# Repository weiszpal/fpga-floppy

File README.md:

# fpga-floppy
FPGA interface board to use an IBM PC floppy disk drive as any C64 comatible FDD

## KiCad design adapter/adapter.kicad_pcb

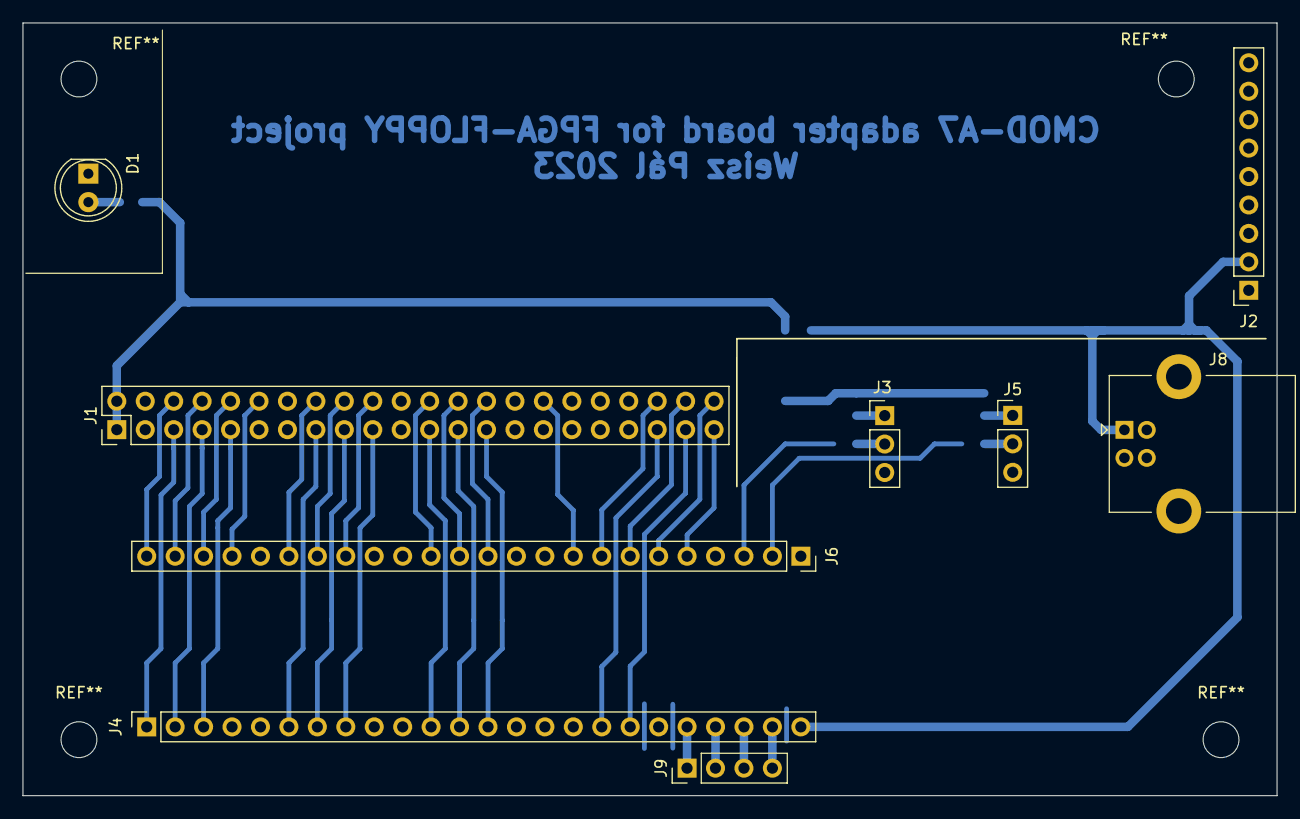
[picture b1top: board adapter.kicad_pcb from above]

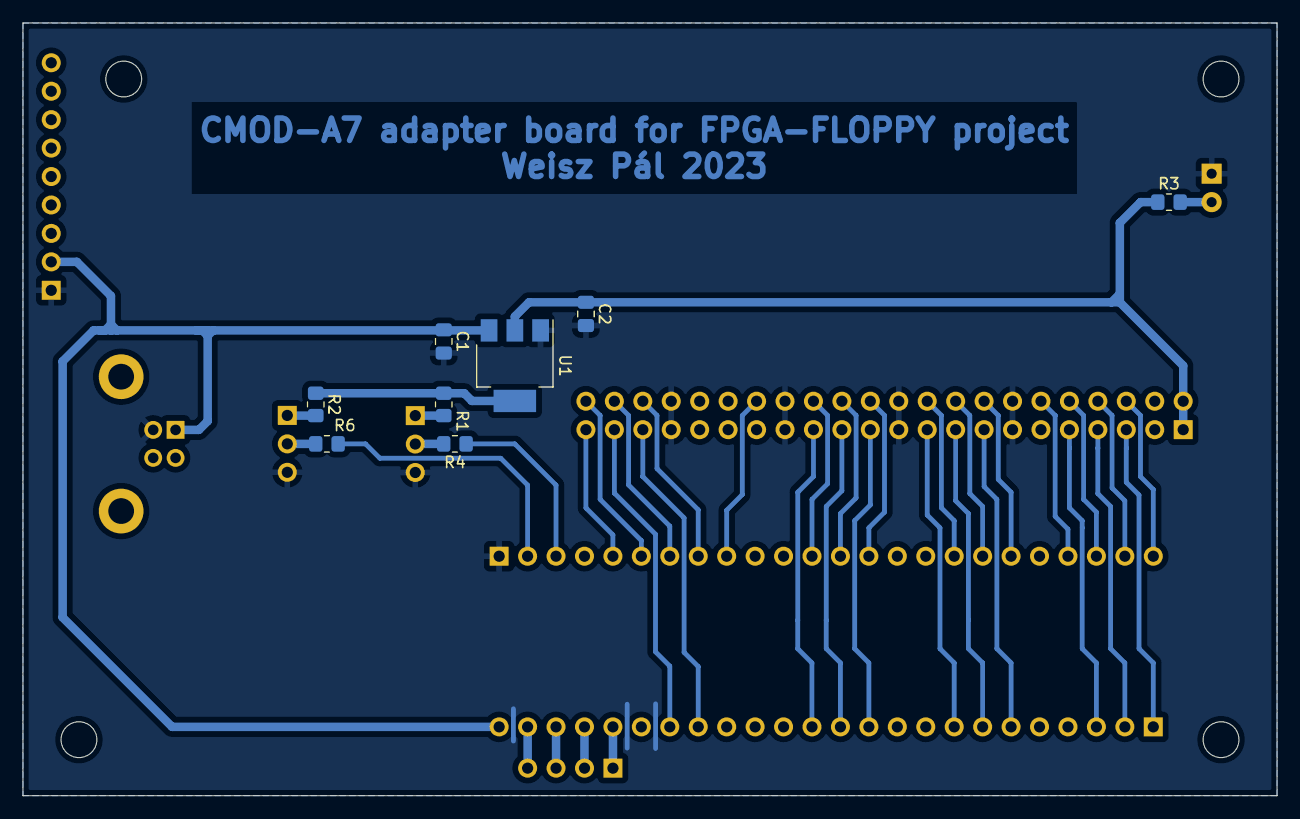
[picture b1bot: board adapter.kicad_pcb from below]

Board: 2 copper layers, 112.0 x 69.0 mm, 17 parts (8 on the bottom side), 40 nets.

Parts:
C1: 100n; C_0805_2012Metric_Pad1.18x1.45mm_HandSolder
C2: 10u; C_0805_2012Metric_Pad1.18x1.45mm_HandSolder
D1: LED_Filled; LED_D5.0mm
J1: FPGA_devboard; PinHeader_2x22_P2.54mm_Vertical
J2: 5V_PWR; PinSocket_1x09_P2.54mm_Vertical
J3: JP1; PinHeader_1x03_P2.54mm_Vertical
J4: CMOD-A7 1; PinSocket_1x24_P2.54mm_Vertical
J5: JP2; PinHeader_1x03_P2.54mm_Vertical
J6: CMOD-A7 2; PinSocket_1x24_P2.54mm_Vertical
J8: USB_B; USB_B_Lumberg_2411_02_Horizontal
J9: DEBUG; PinHeader_1x04_P2.54mm_Vertical
R1, R2, R4, R6: 10k; R_0805_2012Metric_Pad1.20x1.40mm_HandSolder
R3: 1k; R_0805_2012Metric_Pad1.20x1.40mm_HandSolder
U1: AP1117-33; SOT-223-3_TabPin2

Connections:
+3V3: C2.1, J1.1, J1.2, R1.1, R2.1, R3.1, U1.2 (VO)
+5V: C1.1, J2.2, J4.24, J8.1 (VBUS), U1.3 (VI)
/ACTION: J1.5, J4.1
/ATN_IN: J1.7, J4.2
/CLK_IN: J1.9, J4.3
/CLK_OUT: J1.15, J4.6
/DATA_IN: J1.12, J6.21
/DATA_OUT: J1.16, J6.19
/DIR: J1.39, J4.17
/DRVSA: J1.41, J4.18
/DRVSB: J1.42, J6.7
/DSKCHG: J1.24, J6.14
/INDEX: J1.27, J4.13
/MOTEA: J1.43, J6.5
/MOTEB: J1.40, J6.8
/PIO07: J1.17, J4.7
/PIO08: J1.19, J4.8
/PIO11: J1.23, J4.11
/PIO12: J1.25, J4.12
/PIO20: J4.20, J9.1
/PIO21: J4.21, J9.2
/PIO22: J4.22, J9.3
/PIO23: J4.23, J9.4
/PIO26: J6.2, R6.2
/PIO27: J6.3, R4.1
/PIO30: J1.44, J6.6
/PIO33: J1.32, J6.9
/PIO36: J1.28, J6.12
/PIO37: J1.26, J6.13
/PIO41: J1.20, J6.17
/PIO42: J1.18, J6.18
/PIO46: J1.10, J6.22
/PIO47: J1.8, J6.23
/PIO48: J1.6, J6.24
GND: C1.2, C2.2, D1.1 (K), J1.13, J1.14, J1.21, J1.22, J1.29, J1.30, J1.37, J1.38, J2.1, J3.3, J5.3, J6.1, J8.4 (GND), U1.1 (GND)
unnamed: D1.2 (A), R3.2
unnamed: J3.1, R1.2
unnamed: J3.2, R4.2
unnamed: J5.1, R2.2
unnamed: J5.2, R6.1

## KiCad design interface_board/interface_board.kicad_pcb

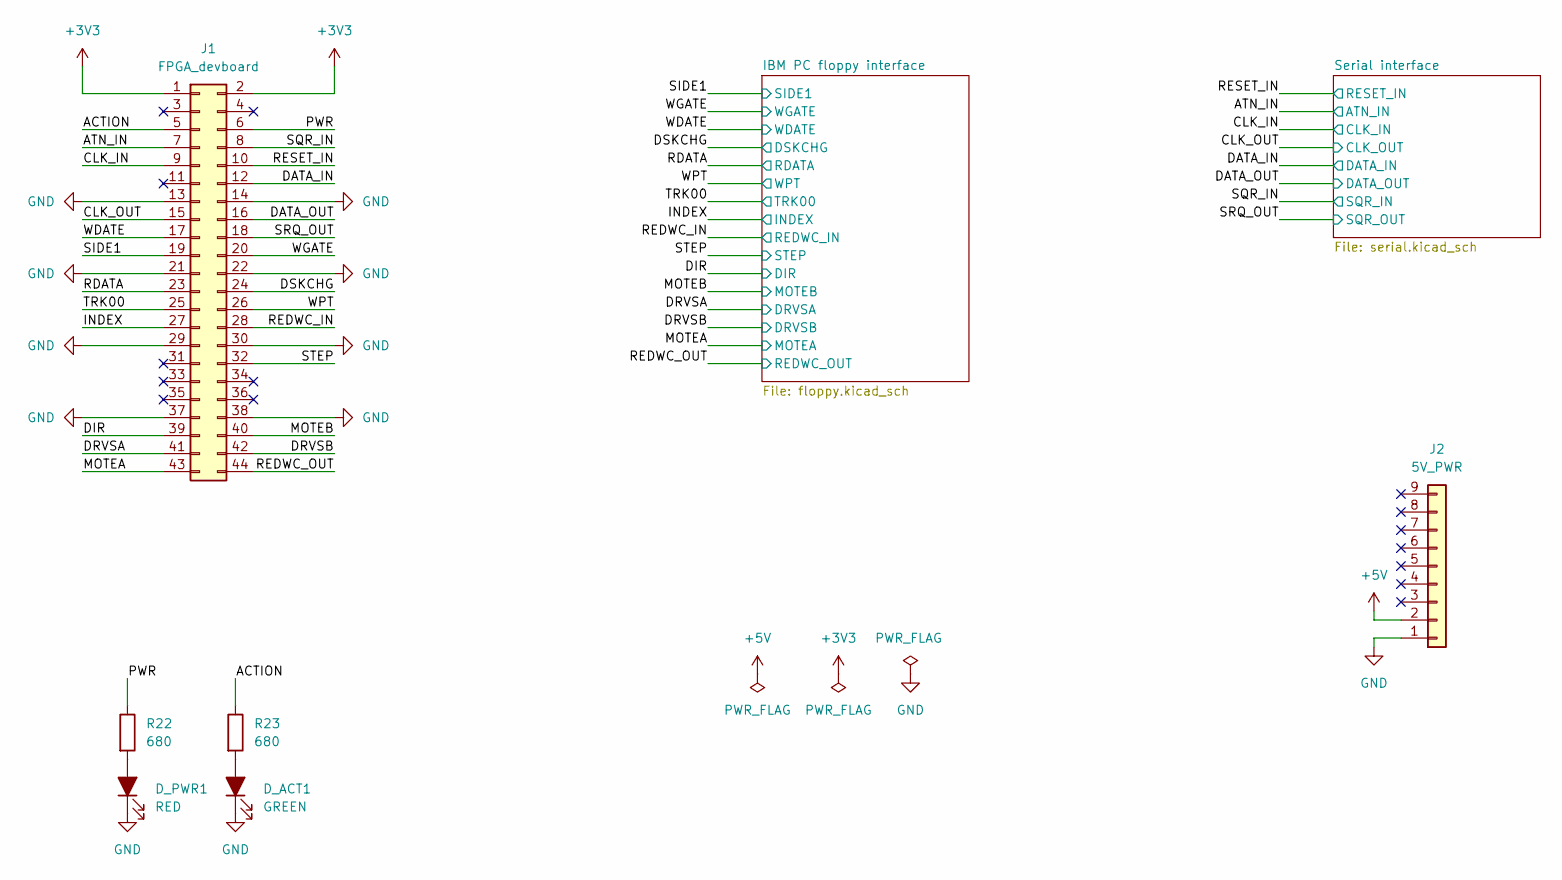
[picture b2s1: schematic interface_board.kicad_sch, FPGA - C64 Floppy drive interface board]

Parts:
D_ACT1: GREEN; LED_0805_2012Metric_Pad1.15x1.40mm_HandSolder
D_PWR1: RED; LED_0805_2012Metric_Pad1.15x1.40mm_HandSolder
J1: FPGA_devboard; PinSocket_2x22_P2.54mm_Vertical
J2: 5V_PWR; PinHeader_1x09_P2.54mm_Vertical
R22, R23: 680; R_0805_2012Metric_Pad1.20x1.40mm_HandSolder

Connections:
+3V3: J1.1, J1.2; also elsewhere on the board
+5V: J2.2; also elsewhere on the board
/ACTION: J1.5, R23.1
/ATN_IN: J1.7; also elsewhere on the board
/CLK_IN: J1.9; also elsewhere on the board
/CLK_OUT: J1.15; also elsewhere on the board
/DATA_IN: J1.12; also elsewhere on the board
/DATA_OUT: J1.16; also elsewhere on the board
/DIR: J1.39; also elsewhere on the board
/DRVSA: J1.41; also elsewhere on the board
/DRVSB: J1.42; also elsewhere on the board
/DSKCHG: J1.24; also elsewhere on the board
/INDEX: J1.27; also elsewhere on the board
/MOTEA: J1.43; also elsewhere on the board
/MOTEB: J1.40; also elsewhere on the board
/PWR: J1.6, R22.1
/RDATA: J1.23; also elsewhere on the board
/REDWC_IN: J1.28; also elsewhere on the board
/REDWC_OUT: J1.44; also elsewhere on the board
/RESET_IN: J1.10; also elsewhere on the board
/SIDE1: J1.19; also elsewhere on the board
/SQR_IN: J1.8; also elsewhere on the board
/SRQ_OUT: J1.18; also elsewhere on the board
/STEP: J1.32; also elsewhere on the board
/TRK00: J1.25; also elsewhere on the board
/WDATE: J1.17; also elsewhere on the board
/WGATE: J1.20; also elsewhere on the board
/WPT: J1.26; also elsewhere on the board
GND: D_ACT1.1 (K), D_PWR1.1 (K), J1.13, J1.14, J1.21, J1.22, J1.29, J1.30, J1.37, J1.38, J2.1; also elsewhere on the board
unnamed: D_ACT1.2 (A), R23.2
unnamed: D_PWR1.2 (A), R22.2

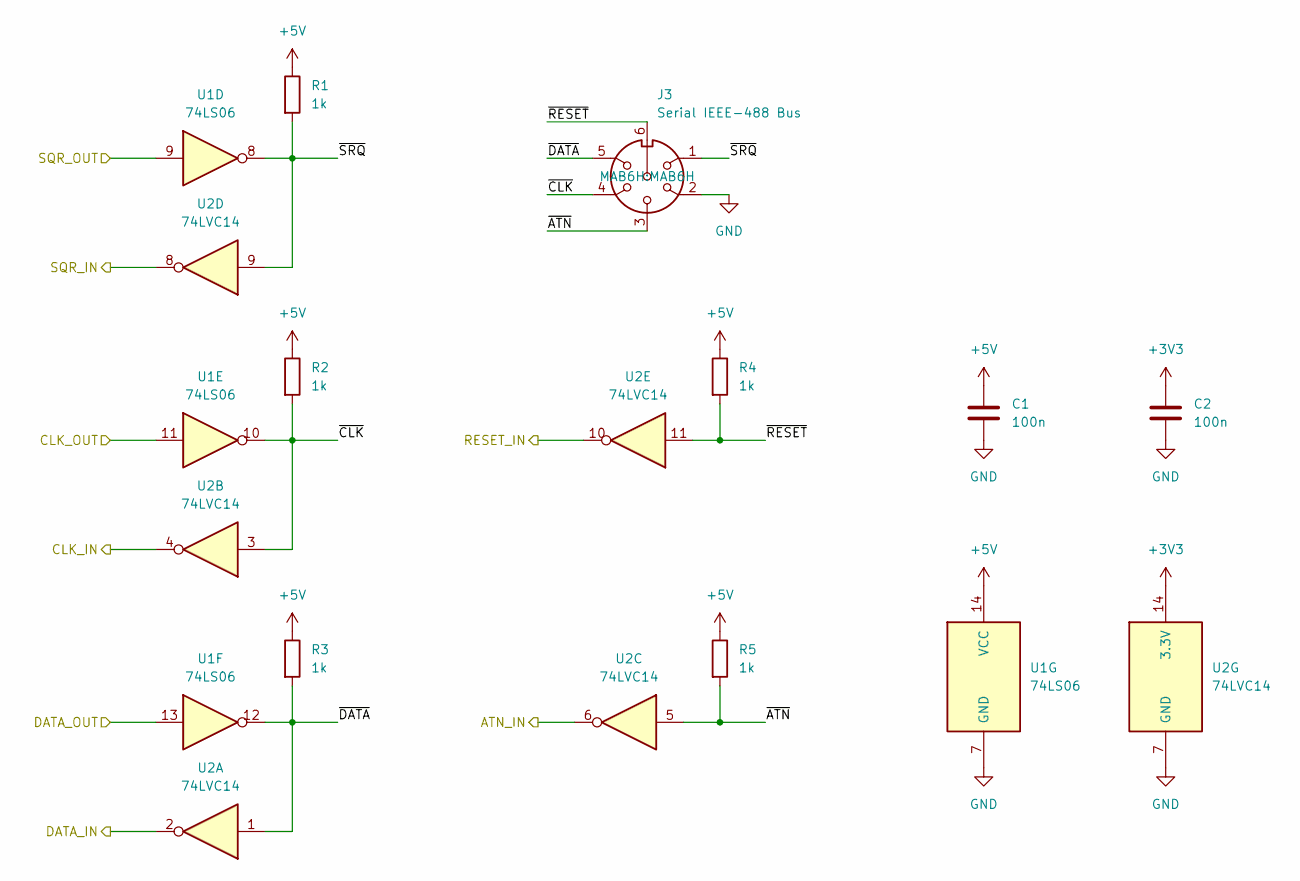
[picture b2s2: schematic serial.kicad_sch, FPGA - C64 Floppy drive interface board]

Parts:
C1, C2: 100n; C_0805_2012Metric_Pad1.18x1.45mm_HandSolder
J3: Serial IEEE-488 Bus; MAB6H
R1, R2, R3, R4, R5: 1k; R_0805_2012Metric_Pad1.20x1.40mm_HandSolder
U1: 74LS06; SOIC-14_3.9x8.7mm_P1.27mm
U2: 74LVC14; SOIC-14_3.9x8.7mm_P1.27mm

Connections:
+3V3: C2.1, U2.14 (3.3V); also elsewhere on the board
+5V: C1.1, R1.1, R2.1, R3.1, R4.1, R5.1, U1.14 (VCC); also elsewhere on the board
/ATN_IN: U2.6; also elsewhere on the board
/CLK_IN: U2.4; also elsewhere on the board
/CLK_OUT: U1.11; also elsewhere on the board
/DATA_IN: U2.2; also elsewhere on the board
/DATA_OUT: U1.13; also elsewhere on the board
/RESET_IN: U2.10; also elsewhere on the board
/SQR_IN: U2.8; also elsewhere on the board
/SRQ_OUT: U1.9; also elsewhere on the board
/Serial interface/~ATN: J3.3, R5.2, U2.5
/Serial interface/~CLK: J3.4, R2.2, U1.10, U2.3
/Serial interface/~DATA: J3.5, R3.2, U1.12, U2.1
/Serial interface/~RESET: J3.6, R4.2, U2.11
/Serial interface/~SRQ: J3.1, R1.2, U1.8, U2.9
GND: C1.2, C2.2, J3.2, U1.7 (GND), U2.7 (GND); also elsewhere on the board

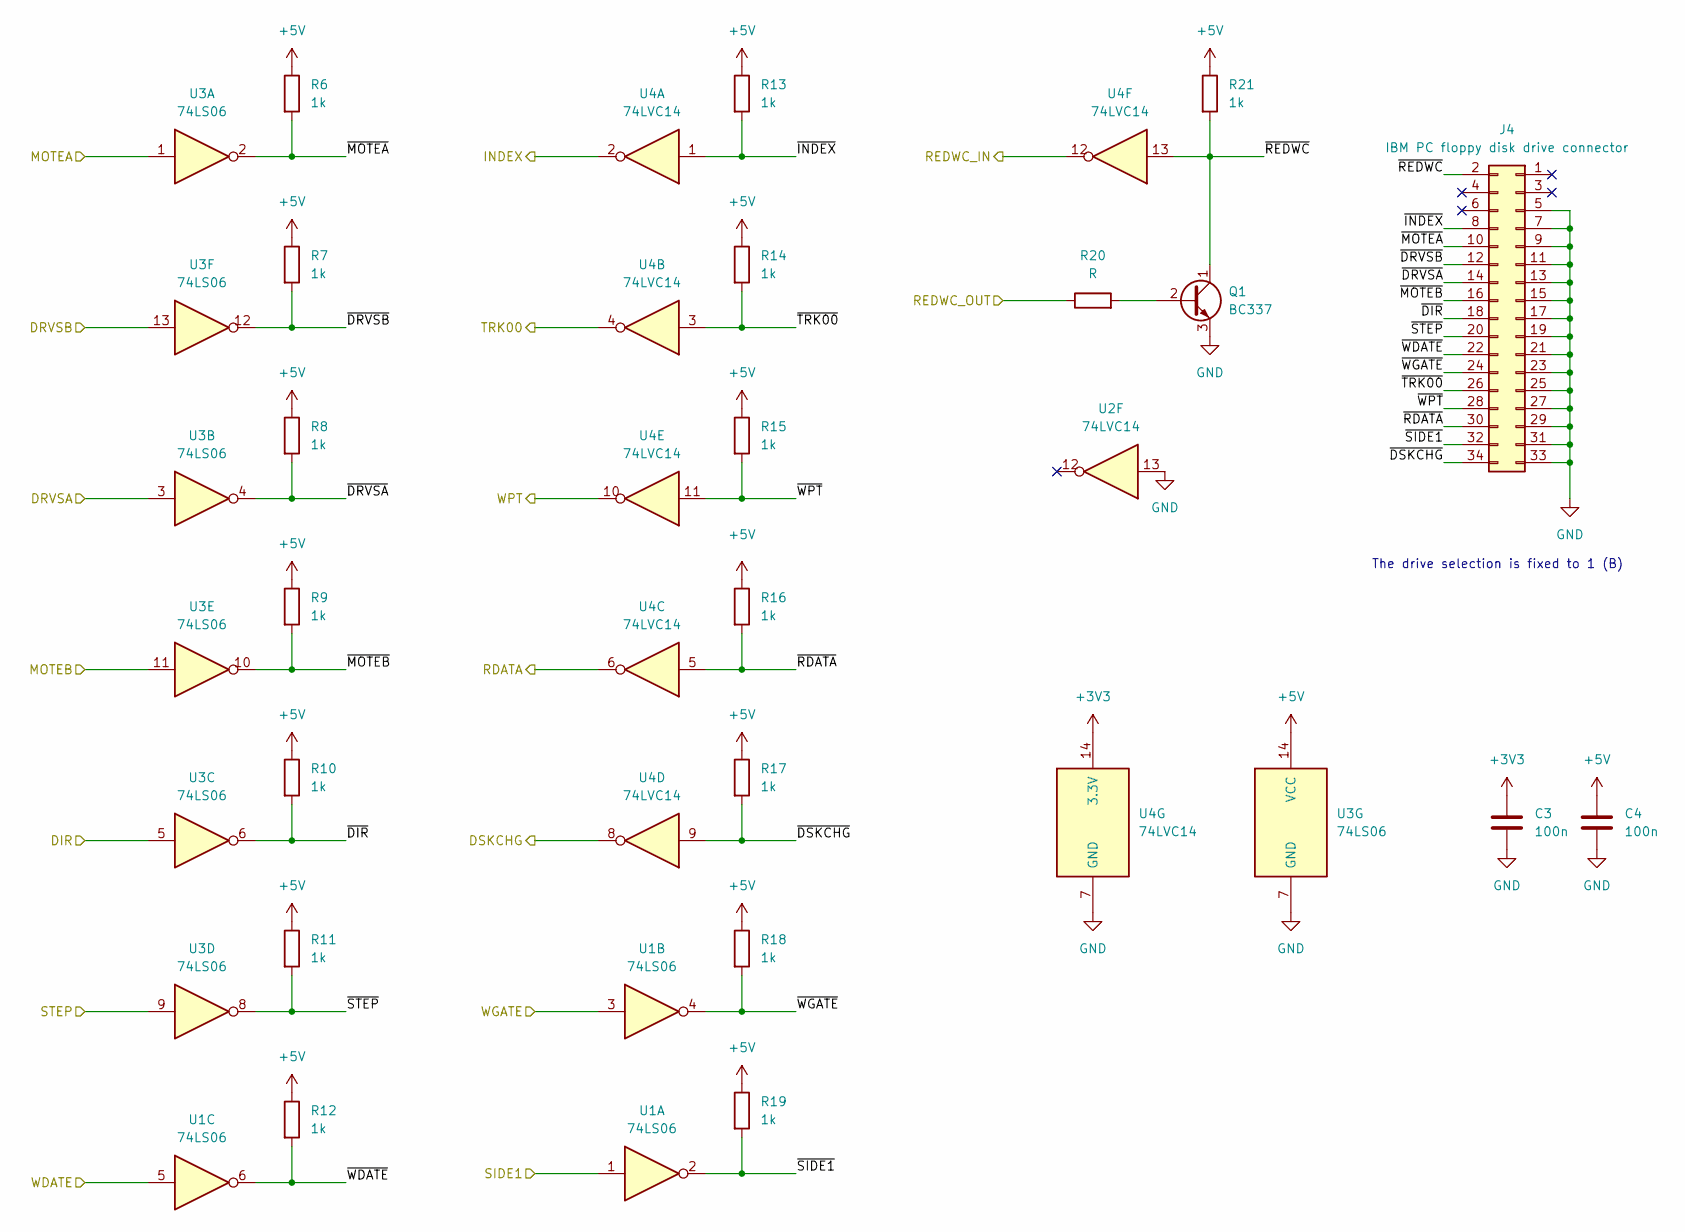
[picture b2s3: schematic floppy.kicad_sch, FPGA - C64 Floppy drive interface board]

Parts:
C3, C4: 100n; C_0805_2012Metric_Pad1.18x1.45mm_HandSolder
J4: IBM PC floppy disk drive connector; IDC-Header_2x17_P2.54mm_Vertical
Q1: BC337; TO-92_Inline_Wide
R6, R7, R8, R9, R10, R11, R12, R13, R14, R15, R16, R17, R18, R19, R21: 1k; R_0805_2012Metric_Pad1.20x1.40mm_HandSolder
R20: R; R_0805_2012Metric_Pad1.20x1.40mm_HandSolder
U1, U3: 74LS06; SOIC-14_3.9x8.7mm_P1.27mm
U2, U4: 74LVC14; SOIC-14_3.9x8.7mm_P1.27mm

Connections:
+3V3: C3.1, U4.14 (3.3V); also elsewhere on the board
+5V: C4.1, R6.1, R7.1, R8.1, R9.1, R10.1, R11.1, R12.1, R13.1, R14.1, R15.1, R16.1, R17.1, R18.1, R19.1, R21.1, U3.14 (VCC); also elsewhere on the board
/DIR: U3.5; also elsewhere on the board
/DRVSA: U3.3; also elsewhere on the board
/DRVSB: U3.13; also elsewhere on the board
/DSKCHG: U4.8; also elsewhere on the board
/IBM PC floppy interface/~DIR: J4.18, R10.2, U3.6
/IBM PC floppy interface/~DRVSA: J4.14, R8.2, U3.4
/IBM PC floppy interface/~DRVSB: J4.12, R7.2, U3.12
/IBM PC floppy interface/~DSKCHG: J4.34, R17.2, U4.9
/IBM PC floppy interface/~INDEX: J4.8, R13.2, U4.1
/IBM PC floppy interface/~MOTEA: J4.10, R6.2, U3.2
/IBM PC floppy interface/~MOTEB: J4.16, R9.2, U3.10
/IBM PC floppy interface/~RDATA: J4.30, R16.2, U4.5
/IBM PC floppy interface/~REDWC: J4.2, Q1.1 (C), R21.2, U4.13
/IBM PC floppy interface/~SIDE1: J4.32, R19.2, U1.2
/IBM PC floppy interface/~STEP: J4.20, R11.2, U3.8
/IBM PC floppy interface/~TRK00: J4.26, R14.2, U4.3
/IBM PC floppy interface/~WDATE: J4.22, R12.2, U1.6
/IBM PC floppy interface/~WGATE: J4.24, R18.2, U1.4
/IBM PC floppy interface/~WPT: J4.28, R15.2, U4.11
/INDEX: U4.2; also elsewhere on the board
/MOTEA: U3.1; also elsewhere on the board
/MOTEB: U3.11; also elsewhere on the board
/RDATA: U4.6; also elsewhere on the board
/REDWC_IN: U4.12; also elsewhere on the board
/REDWC_OUT: R20.1; also elsewhere on the board
/SIDE1: U1.1; also elsewhere on the board
/STEP: U3.9; also elsewhere on the board
/TRK00: U4.4; also elsewhere on the board
/WDATE: U1.5; also elsewhere on the board
/WGATE: U1.3; also elsewhere on the board
/WPT: U4.10; also elsewhere on the board
GND: C3.2, C4.2, J4.5, J4.7, J4.9, J4.11, J4.13, J4.15, J4.17, J4.19, J4.21, J4.23, J4.25, J4.27, J4.29, J4.31, J4.33, Q1.3 (E), U2.13, U3.7 (GND), U4.7 (GND); also elsewhere on the board
unnamed: Q1.2 (B), R20.2

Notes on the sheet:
The drive selection is fixed to 1 (B)

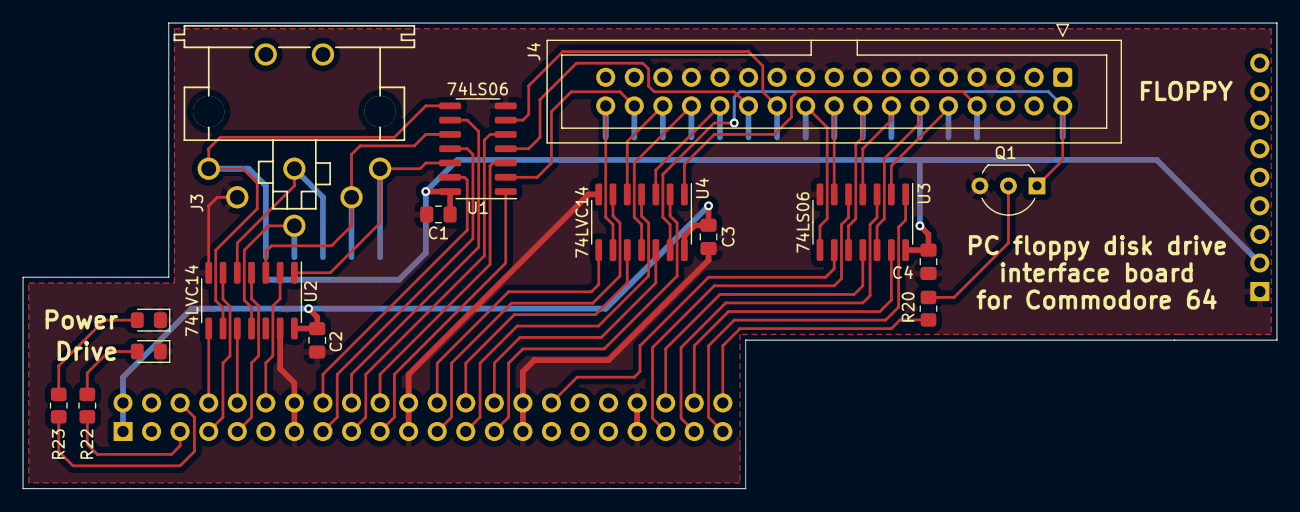
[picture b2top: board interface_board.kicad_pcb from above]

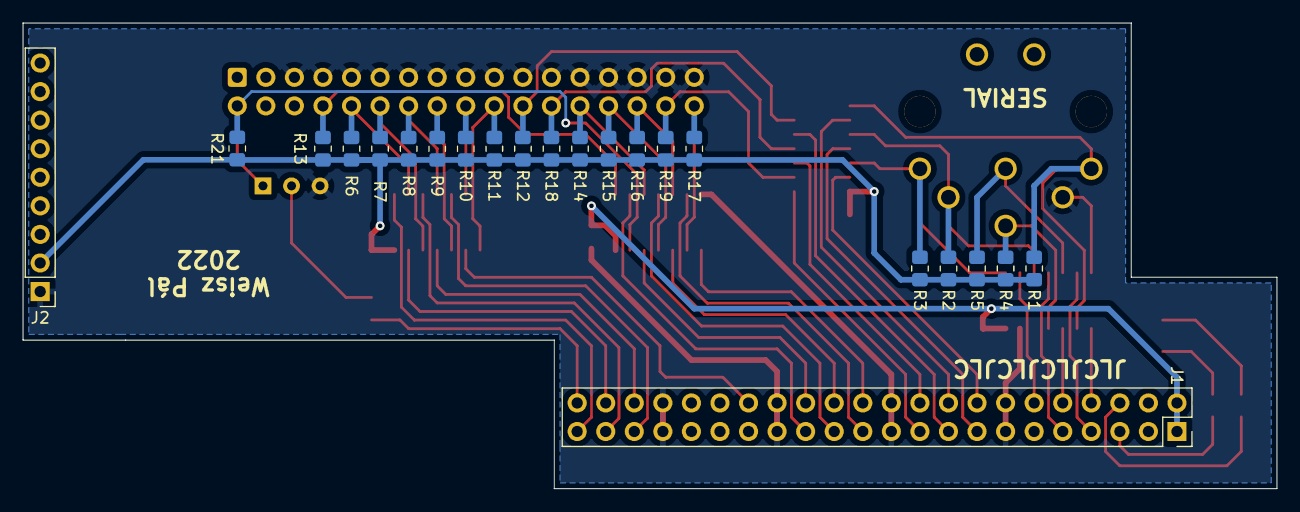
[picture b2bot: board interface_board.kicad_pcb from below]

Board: 2 copper layers, 111.5 x 41.4 mm, 38 parts (22 on the bottom side), 52 nets.

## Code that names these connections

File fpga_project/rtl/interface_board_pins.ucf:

NET "fpga_clk" 	LOC="p126";	//50 MHz clock

// SERIAL IN - ok
NET "DATA_IN"		LOC="p121" | PULLUP;	//DATA_IN
NET "CLK_IN"		LOC="p120" | PULLUP;	//CLK_IN
NET "RESET_IN"		LOC="p119" | PULLUP | CLOCK_DEDICATED_ROUTE = FALSE; //RESET_IN
NET "ATN_IN"		LOC="p118" | PULLUP;	//ATN_IN
NET "SRQ_IN"		LOC="p117" | PULLUP;	//SRQ_IN

// SERIAL OUT - ok
NET "SRQ_OUT" 		LOC="p132";	//SRQ_OUT
NET "CLK_OUT" 		LOC="p131";	//CLK_OUT
NET "DATA_OUT" 	LOC="p124";	//DATA_OUT

// FLOPPY IN - ok
NET "INDEX"			LOC="p143" | PULLUP;	//INDEX
NET "REDWC_IN"		LOC="p142" | PULLUP;	//REDWC_IN
NET "TRK00"			LOC="p141" | PULLUP;	//TRK00
NET "WPT"			LOC="p140" | PULLUP;	//WPT
NET "DSKCHG"		LOC="p138" | PULLUP;	//DSKCHG
NET "RDATA"			LOC="p139" | PULLUP;	//RDATA

// FLOPPY OUT - ok
NET "REDWC_OUT"	LOC="p12";	//REDWC_OUT
NET "SIDE1"	 		LOC="p137";	//SIDE1
NET "WGATE" 		LOC="p134";	//WGATE
NET "WDATE" 		LOC="p133";	//WDATE
NET "STEP" 			LOC="p1";	//STEP
NET "DIR" 			LOC="p8";	//DIR
NET "MOTEB" 		LOC="p9";	//MOTEB
NET "DRVSA" 		LOC="p11";	//DRVSA
NET "DRVSB" 		LOC="p10";	//DRVSB
NET "MOTEA" 		LOC="p14";	//MOTEA

// LEDS - ok
NET "PWR_LED" 		LOC="p115";	//POWER LED
NET "ACTION_LED"	LOC="p116";	//DRIVE LED

// SWITCHES
NET "SW0"			LOC="p16";	//SWITCH 0
NET "SW1"			LOC="p17";	//SWITCH 1

// Debug
NET "DBG_RST"		LOC="p5";
NET "DBG_PI2"		LOC="p7";
NET "DBG_MO"		LOC="p2";	
NET "DBG_RDY"		LOC="p6";

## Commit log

2022-09-04 Add empty kicad project
2022-09-07 Add interface board PCB design
2022-09-14 Finish interface board PCB
2022-09-19 Add RAM, ROM, clock generator and FDC modules to fpga project
2022-09-19 Test RAM module
2022-09-20 Modify and test RAM to use separate data lines, add CPU and CIA
2022-10-03 Complete and test pin configuration file
2022-10-03 Test RAM and ROM modules
2022-10-04 Add bus test
2022-10-04 Make project directory structured
2022-10-04 Get rid of unneccessary report files
2022-10-06 Add top module
2022-10-10 Add logic analyzer config files
2022-10-11 Minor cleanup in top module, add ucf file
2022-10-12 Split FDC databus to separate DATA_IN and DATA_OUT lines
2022-10-12 First ynthesis
2022-10-17 CPU sort of works with improved clock generator
2022-10-17 RAM and ROM test success in simulation
2022-10-19 Add external logic analyzer measurement, found weird bug
2022-10-24 Shorten simulation time using fake feedback signals on index line
2022-11-04 Add 6502 emulator written in C and fix B flag logic in T65 core implementation
2022-11-06 Add rudimentary IEC serial protocol decoder script to digital analyzer waveforms
2022-11-07 Improve serial protocol analyzer script
2022-11-20 Record several measurements
2022-11-22 Add PLL for 16 MHz system clk
2022-11-24 Fix DSKCHG pin assignment in ucf file, flip ribbon cable connector on schematic
2022-12-04 Add more measurements about startup, improve emu script
2022-12-04 Add schematics for appendix, add sketch to diploma, simulate startup in isim
2022-12-05 Add some more debug features to emulator, fix clock testbench for PLL testing
2022-12-09 Inspect startup process, synchronize CMD_WR in FDC implementation, comment emulator
2022-12-09 Clean up repository
2022-12-10 Add half-written presentation
2022-12-11 Almost complete presentation
2022-12-15 Do presentation, add introduction and protocol description to documentation
2022-12-15 Add interface board and digital designing to documentation
2022-12-15 Add CIA and CPU functional description
2022-12-16 Complete hardware design modules description in documentation
2022-12-17 Add pictures and finish hardver design description
2022-12-18 Add firmware and emulator description in decumentation
2022-12-18 Submit documentation
2023-01-18 Add adapter board design
